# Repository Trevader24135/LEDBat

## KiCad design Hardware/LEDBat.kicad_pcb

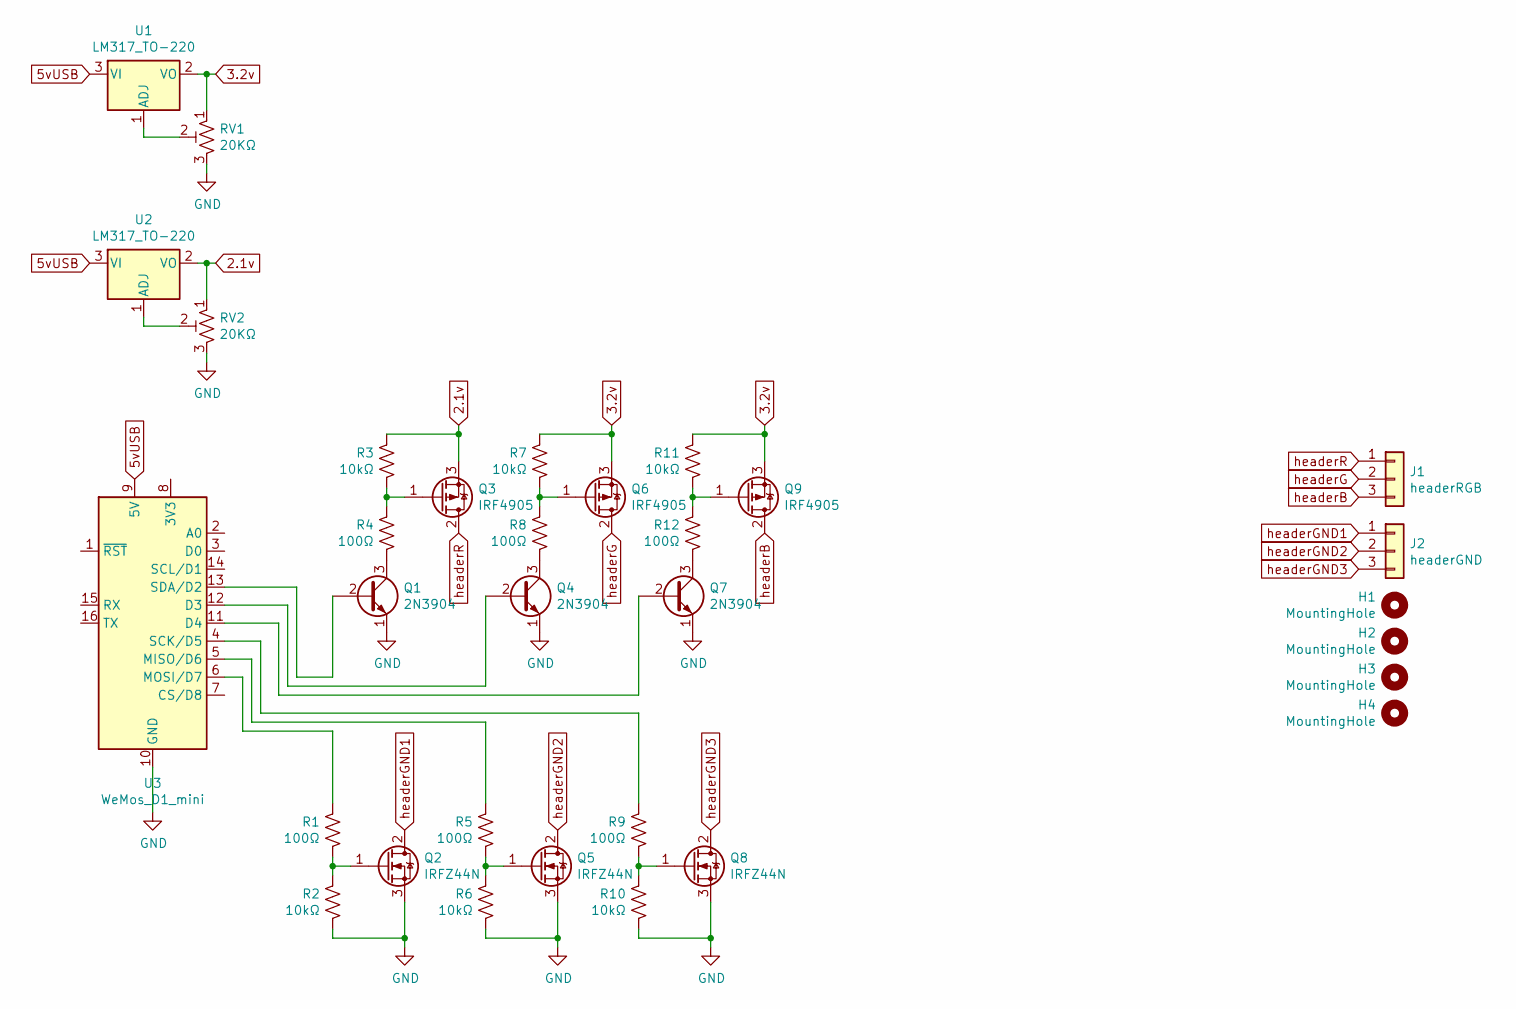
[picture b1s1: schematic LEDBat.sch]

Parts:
H1, H2, H3, H4: MountingHole; MountingHole_3.2mm_M3
J1: headerRGB; PinHeader_1x03_P2.54mm_Vertical
J2: headerGND; PinHeader_1x03_P2.54mm_Vertical
Q1, Q4, Q7: 2N3904; TO-92_Inline
Q2, Q5, Q8: IRFZ44N; TO-220-3_Vertical
Q3, Q6, Q9: IRF4905; TO-220-3_Vertical
R1, R4, R5, R8, R9, R12: 100Ω; R_Axial_DIN0204_L3.6mm_D1.6mm_P7.62mm_Horizontal
R2, R3, R6, R7, R10, R11: 10kΩ; R_Axial_DIN0204_L3.6mm_D1.6mm_P7.62mm_Horizontal
RV1, RV2: 20KΩ; Potentiometer_Bourns_3296W_Vertical
U1, U2: LM317_TO-220; TO-220-3_Vertical
U3: WeMos_D1_mini; WEMOS_D1_mini_light

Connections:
2.1v: Q3.3 (S), R3.2, RV2.1, U2.2 (VO)
3.2v: Q6.3 (S), Q9.3 (S), R7.2, R11.2, RV1.1, U1.2 (VO)
5vUSB: U1.3 (VI), U2.3 (VI), U3.9 (5V)
GND: Q1.1 (E), Q2.3 (S), Q4.1 (E), Q5.3 (S), Q7.1 (E), Q8.3 (S), R2.1, R6.1, R10.1, RV1.3, RV2.3, U3.10 (GND)
unnamed: Q1.2 (B), U3.13 (SDA/D2)
unnamed: Q1.3 (C), R4.1
unnamed: Q2.1 (D), R1.1, R2.2
unnamed: Q3.1 (G), R3.1, R4.2
unnamed: Q4.2 (B), U3.12 (D3)
unnamed: Q4.3 (C), R8.1
unnamed: Q5.1 (D), R5.1, R6.2
unnamed: Q6.1 (G), R7.1, R8.2
unnamed: Q7.2 (B), U3.11 (D4)
unnamed: Q7.3 (C), R12.1
unnamed: Q8.1 (D), R9.1, R10.2
unnamed: Q9.1 (G), R11.1, R12.2
unnamed: R1.2, U3.6 (MOSI/D7)
unnamed: R5.2, U3.5 (MISO/D6)
unnamed: R9.2, U3.4 (SCK/D5)
unnamed: RV1.2, U1.1 (ADJ)
unnamed: RV2.2, U2.1 (ADJ)
headerB: J1.3, Q9.2 (D)
headerG: J1.2, Q6.2 (D)
headerGND1: J2.1, Q2.2 (G)
headerGND2: J2.2, Q5.2 (G)
headerGND3: J2.3, Q8.2 (G)
headerR: J1.1, Q3.2 (D)

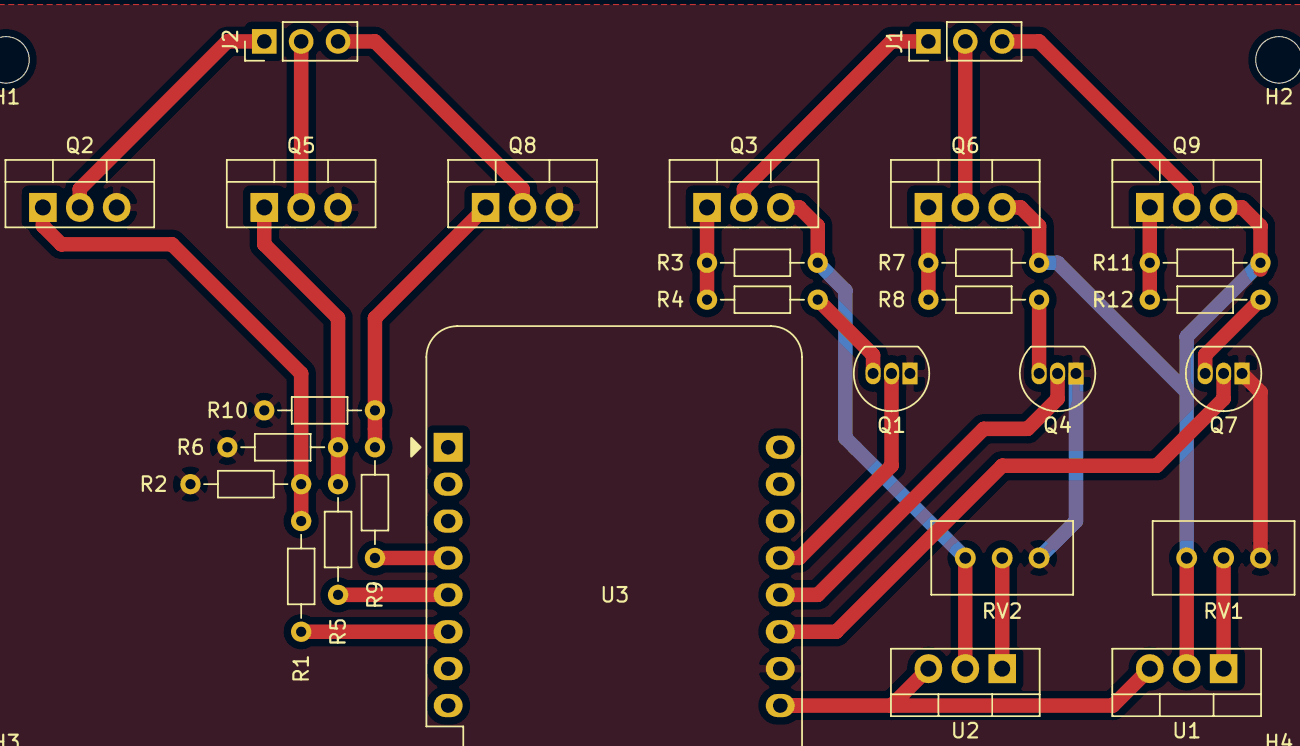
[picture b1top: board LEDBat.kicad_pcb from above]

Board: 2 copper layers, 32 parts (0 on the bottom side), 27 nets.

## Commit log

2021-10-11 Initial work commit
